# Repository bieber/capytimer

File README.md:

# CapyTimer

CapyTimer is meant to be a simple timer for
boxing/kickboxing/grappling/fitness.  My goal is to keep its interface
as simple as possible while maintaining the most important
functionality.  Work and rest times are set with dials, and the timing
started and stopped with a switch or button.  The display counts the
remaining time, the current round, and nothing else.

The display is constructed from WS2812B addressable LEDs.  The
original plan was to cut up and solder three-LED sections to create
the digits, but that proved time consuming and ugly so I ultimately
designed a PCB for the digits with the LEDs pre-placed.  You can
follow the original plan and save some money by cutting up and
soldering a WS2812B strip, or just order the PCBs preassembled from
JLC (or just get the boards manufactured and solder on the LEDs
yourself).

This isn't really meant to be a prescriptive set of instructions for
building the timer exactly a certain way.  I've provided components
here and I'll lay out a general path towards putting it together, but
you should feel free to substitute different controls and alter the
presentation to your liking.

**Warning** - The remote control design is currently untested.  I
*think* the parts will all fit properly, but I'm still waiting on the
final PCBs to test with and can't guarantee that the design works yet.

## Directory Structure

* `3d/` - Files for 3D printing.  These include the digit and
  separator diffusers, the remote control body, and a set of printed
  frames to hold the digits for testing purposes.
* `firmware/` - Code to run the AVR microcontroller.  Specifically
  this expects an Atmega328P, the avr-gcc toolchain and a USBasp
  programmer.  If you deviate from these specifications you may need
  to alter the firmware and makefile.
* `pcb/` - KiCad schematics and PCB designs.  This includes the main
  control board, boards with the LEDs laid out for the digits and
  separator, and a control board for the remote control.  With the
  exception of the remote control board (which is simple enough to
  easily hand solder), I've included gerbers and BOM/placement files
  that you can use to have the boards manufactured by JLCPCB.  These
  worked as of this publishing, but be warned that some parts may go
  out of stock and need replacing (they already switched to a new
  version of the WS2812B LEDs while I was working on the boards).
* `enclosure` - SVG designs to cut a front for the timer using the
  Shaper Origin.  You'll have to adapt these if you use a different
  CNC.

## Assembly Instructions

Please don't consider these instructions exhaustive, but more general
guidance.  You'll want to have some experience with electronics,
soldering and crimping connectors before getting started on this, as
well as some way to build an enclosure for the timer (I build mine out
of wood).

### Materials

| Part | Qty |
| ---- | --- |
| Control Board | 1 |
| Digit Board | 6 |
| Separator Board | 1 |
| Digit Diffuser | 6 |
| Separator Diffuser | 1 |
| M3x4.6x5.7mm Heat Set Inserts | 17 |
| M3x6 Screw | 14 |
| Linear Potentiometer (somewhere in the neighborhood of 10k) | 4 |
| Push Button | 2 |
| JST-PH Connector (3 pin) | 20 |
| JST-PH Connector (2 pin) | 4 |
| DC Barrel Connector | 1 |
| Right Angle Header (Female, 2.54mm) | 14 pins |
| Header (Male, 2.54mm) | 3 pins |
| Header Jumper | 1 |
| AVR-ISP 6 Pin Box Header | 1 |
| 3386P Potentiometer | 2 |
| 10k Through Hole Resistor | 2 |
| QIACHIP 433Mhz Transmitter/Receiver Set | 1 |
| Remote Control Parts | 1 set |
| M3x12 Screw | 3 |
| 5x1mm Round Magnet | 8 |
| AAA Battery Contact Plate | 4 |

Note that this doesn't include surface-mount components on the PCB,
only the parts you'll need to manually assemble.  If you intend to
hand solder the PCBs, consult the schematics for part listings.

### The Display

The display uses six digits and one separator between the minutes and
seconds.  You can have the digits and separator LEDs pre-assembled on
a PCB by JLCPCB using the files in the `pcb/` directory, or you can
buy a strip of WS2812B LEDs and glue them into the 3D printed
diffusers.  If you do so, you'll want to use 3 LEDs per digit segment
and one for each of the dots in the separator.  The LEDs should be
laid out in the same order that segments normally come in a seven
segment display.

If you get your LED PCBs pre-assembled, you'll still need to solder on
the connectors.  Use one three-pin JST-PH connector for each
connection.  Be sure to solder these on the back side of the board so
you can plug in to them while the front of the board is seated in the
diffuser.

When printing the plastic diffusers, I like to use white filament for
the first few layers and then switch to black.  This will minimize
light bleeding between segments while the display is in use.  If you
use PCBs for the digits and separator, the diffusers have holes for
threaded inserts.  You can then use the M3x6 screws to attach the
boards to the diffusers.

### The Control Board

Assuming you get the control board assembled by JLCPCB or some other
manufacturer, you'll just need to solder the connectors and a few
potentiometers onto the control board.  These include the DC barrel
jack for power, JST-PH connections for the screen, potentiometers and
push buttons, the AVR-ISP header, the header for the diagnostic jumper
(optional) and the angled header for the QIACHIP receiver module
(optional, only required if you want to use the remote control).  The
two 3386P potentiometers are used for volume and brightess control and
should be soldered directly onto the board.

The `JRESET1` connector is currently unused and can be safely ignored.

To program the microcontroller, just connect the ISP header to a
USBasp programmer.  You'll need the avr-gcc toolchain and avrdude
installed.  You can then run `make fuse` to program the fuses on the
chip, and `make program` to transfer the firmware.  After that the
timer should just work when everything is plugged in.

### Connections

* Solder a DC barrel jack connector onto `J1` for power.
* Connect four potentiometers to the 3-pin JST-PH connectors on the
  top-left corner of the board.  These will set the minutes and
  seconds for the work and rest periods.  The names on the silk screen
  are abbreviations for the function of the potentiometer, e.g. `JWM1`
  is the connection for the potentiometer that controls the minutes of
  the work period.  For these connectors, pin 1 is ground, pin 2 is
  signal, and pin 3 is +5v.
* The display connects to `JOUT1` and `JOUT2` via 3-pin JST-PH
  connectors.  Pin 1 is ground, pin 2 is signal, pin 3 is +5v.  As
  long as you connect the same pins on each end of your cables
  everything should work.  The WS2812B LEDs are daisy chained, so
  `JOUT1` should connect to the `JIN1` connector of the first digit,
  then its `JOUT1` connector should connect to the `JOUT1` of the next
  digit, and so on.  Connect the digits and separator for the time
  first, and then the two digits for the round display.  Finally, you
  can connect `JOUT1` on the last digit to `JOUT2` on the control
  board.  This final connection is for power only, to reduce the
  current that needs to flow through the first connection between
  control board and digits.
* The start and stop buttons should connect to the 2-pin JST-PH
  connectors labeled `JSTART1` and `JSTOP1`.  `JRESET1` is unused.
  These connectors have no polarity, they just need to be normally
  open and close when the buttons are pushed.
* Connect an active piezo buzzer to the 2-pin JST-PH connector labeled
  `JBUZZ1`.
* You may optionally solder a 3 pin male header to `JDIAG1`.  Place a
  jumper across the right two pins for normal operation: shifting the
  jumper to the left will put the timer in diagnostic mode, which
  displays the raw ADC value from the work minutes potentiometer for
  debugging purposes.
* If you intend to use a remote control, solder 7 pin female header,
  preferably right-angle, to `JRF1`.  You can then insert a QIACHIP
  receiver module directly into the header.

### Enclosure

The enclosure is largely left as an exercise for the reader.  You'll
want to select potentiometers and push buttons that fit your desired
aesthetic, and you may also wish to add features like an on/off switch
and external power inlet to the enclosure.

Because of the size of the timer, I haven't included a 3D printed
enclosure design.  Even with a 400x400 print bed, it would be
prohibitive to fit all six digits and the controls.  I have, however,
included two 3D printed frames that can hold the digit diffusers up
(with CA glue).  These aren't suitable for production use, but served
me well during development.

For production use, I build my enclosures as open-backed wooden boxes
with a front panel that has pockets routed in for the digit diffusers,
controls and the piezo buzzer.  I use a Shaper Origin to make the cuts
in the front panel, and you can find the SVG files for my design in
the `enclosure/` directory.  I've only tested these with the Shaper,
and expect that other CNCs will probably need some work to adapt them.

### Remote Control (Optional)

With a QIACHIP receiver and transmitter set, you can also build a
remote control for your timer.  The `pcb/` directory includes a small
PCB to tie the QIACIP transmitter to some tactile push button switches
and two AAA batteries.

For the remote control board, you'll need to solder on two pull-up
resistors, two tactile push-button switches (use switches tall enough
to poke up through the remote body), and a connector for the batteries
(or just solder the battery connectors directly to the board).  Add
right-angle header for the QIACHIP transmitter, and solder on an
antenna to `JANT1`.

The top remote component has holes for three heat-set inserts and four
5x1mm magnets, which should be glued into place.  You'll also want to
glue in the four battery contact plates, alternating positive and
negative plates between the two battery slots.  Solder the two plates
at the bottom of the remote together, and then solder wires on to the
connectors towards the top.

Glue opposite-polarity magnets into the remote lid to hold it on to
the body.  You can then attach the PCB and the remote body bottom to
the top by using the three M3x12 screws.  This connection is
inherently weak because the stems holding everything together are
stressed perpendicular to their layers, so be careful not to tighten
the screws more than necessary to hold everything together.

## Afterword

This should give you a rough idea of how to assemble one of these
timers, but the instructions aren't exceedingly detailed and leave a
lot of room to make the project your own.  If you attempt to build one
and run into problems, feel free to submit an issue.  And if you come
up with a design improvement, pull requests are welcome.

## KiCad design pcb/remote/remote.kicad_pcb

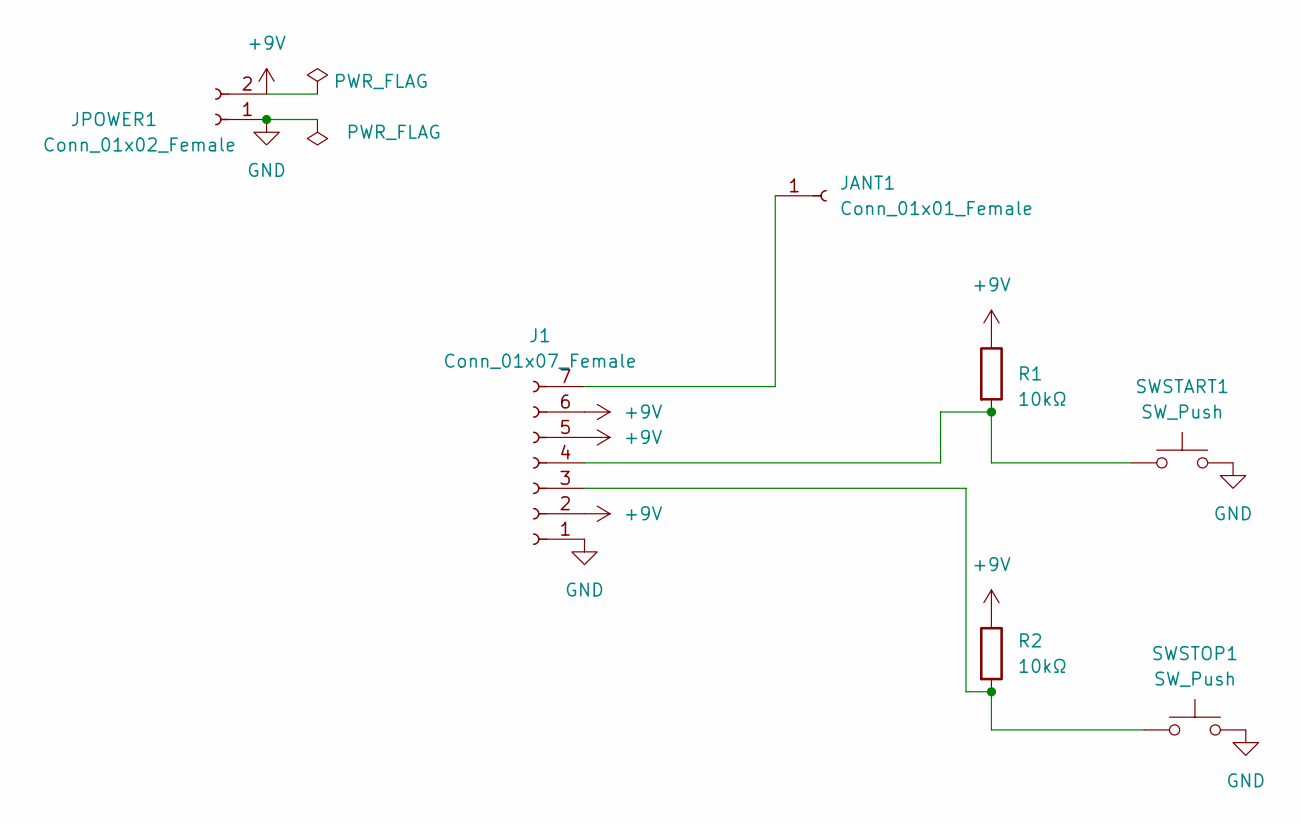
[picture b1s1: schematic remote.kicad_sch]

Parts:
J1: Conn_01x07_Female; PinHeader_1x07_P2.54mm_Vertical
JANT1: Conn_01x01_Female; PinHeader_1x01_P2.54mm_Vertical
JPOWER1: Conn_01x02_Female; JST_PH_B2B-PH-K_1x02_P2.00mm_Vertical
R1, R2: 10kΩ; R_Axial_DIN0207_L6.3mm_D2.5mm_P10.16mm_Horizontal; LCSC C25804
SWSTART1: SW_Push; SW_PUSH_6mm
SWSTOP1: SW_Push; SW_PUSH_6mm

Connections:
+9V: J1.2, J1.5, J1.6, JPOWER1.2, R1.1, R2.1
GND: J1.1, JPOWER1.1, SWSTART1.2, SWSTOP1.2
unnamed: J1.3, R2.2, SWSTOP1.1
unnamed: J1.4, R1.2, SWSTART1.1
unnamed: J1.7, JANT1.1

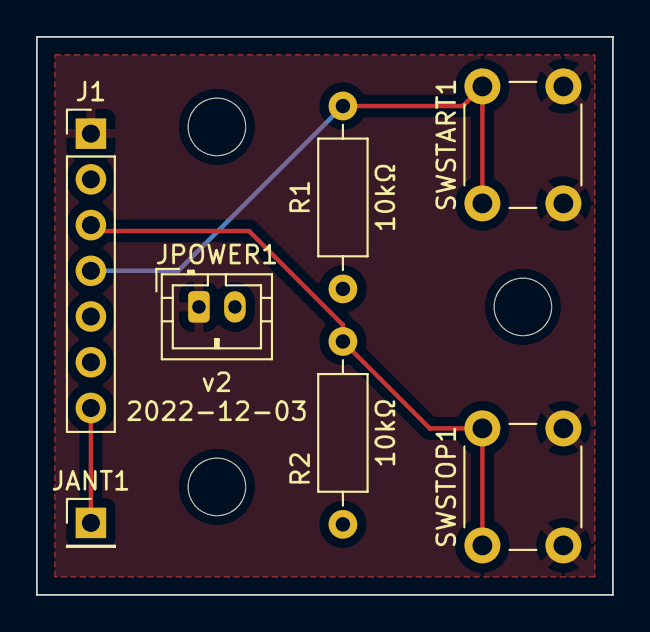
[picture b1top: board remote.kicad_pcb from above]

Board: 2 copper layers, 32.0 x 31.0 mm, 7 parts (0 on the bottom side), 5 nets.

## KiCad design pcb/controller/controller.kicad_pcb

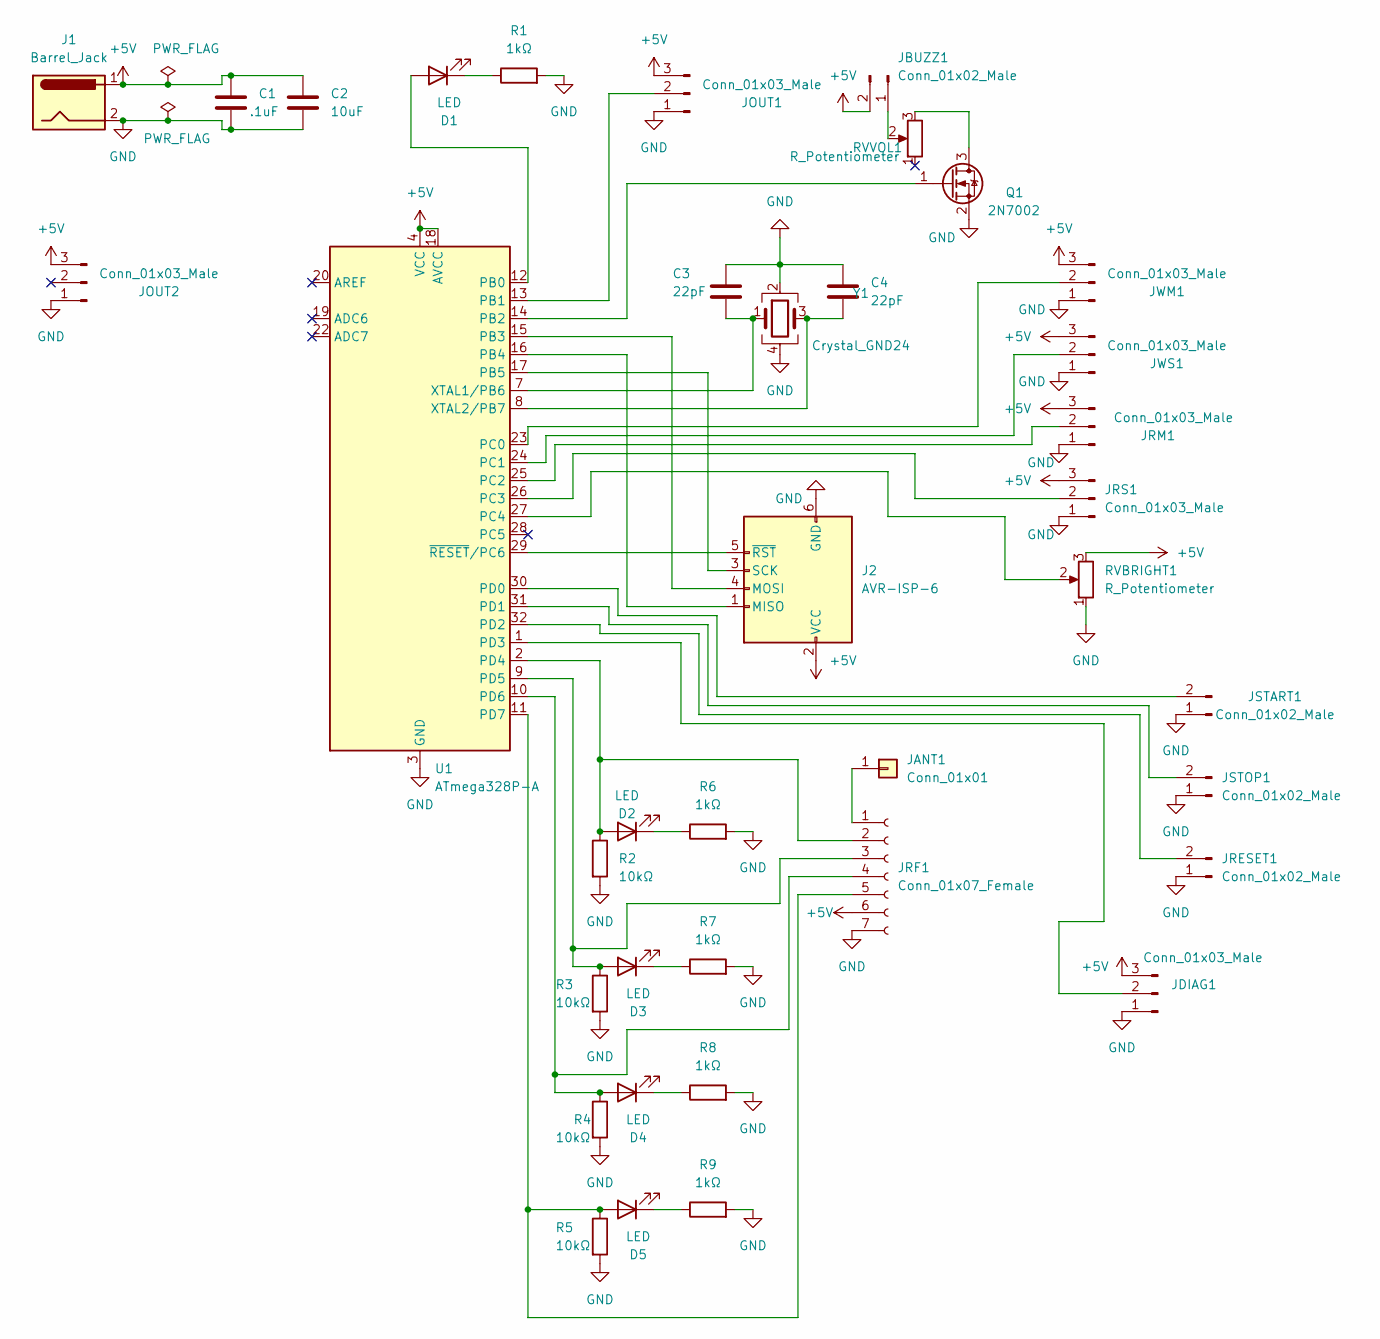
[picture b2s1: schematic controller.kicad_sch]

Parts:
C1: .1uF; C_0603_1608Metric; LCSC C14663
C2: 10uF; C_0805_2012Metric; LCSC C15850
C3, C4: 22pF; C_0402_1005Metric; LCSC C1555
D1, D2, D3, D4, D5: LED; LED_0805_2012Metric; LCSC C2297
J1: Barrel_Jack; BarrelJack_Horizontal
J2: AVR-ISP-6; IDC-Header_2x03_P2.54mm_Vertical
JANT1: Conn_01x01; PinHeader_1x01_P2.54mm_Vertical
JBUZZ1: Conn_01x02_Male; JST_PH_B2B-PH-K_1x02_P2.00mm_Vertical
JDIAG1: Conn_01x03_Male; PinHeader_1x03_P2.54mm_Vertical
JOUT1, JOUT2: Conn_01x03_Male; JST_PH_B3B-PH-K_1x03_P2.00mm_Vertical
JRESET1: Conn_01x02_Male; JST_PH_B2B-PH-K_1x02_P2.00mm_Vertical
JRF1: Conn_01x07_Female; PinHeader_1x07_P2.54mm_Vertical
JRM1: Conn_01x03_Male; JST_PH_B3B-PH-K_1x03_P2.00mm_Vertical
JRS1: Conn_01x03_Male; JST_PH_B3B-PH-K_1x03_P2.00mm_Vertical
JSTART1: Conn_01x02_Male; JST_PH_B2B-PH-K_1x02_P2.00mm_Vertical
JSTOP1: Conn_01x02_Male; JST_PH_B2B-PH-K_1x02_P2.00mm_Vertical
JWM1: Conn_01x03_Male; JST_PH_B3B-PH-K_1x03_P2.00mm_Vertical
JWS1: Conn_01x03_Male; JST_PH_B3B-PH-K_1x03_P2.00mm_Vertical
Q1: 2N7002; SOT-23; LCSC C8545
R1, R6, R7, R8, R9: 1kΩ; R_0603_1608Metric; LCSC C21190
R2, R3, R4, R5: 10kΩ; R_0603_1608Metric; LCSC C25804
RVBRIGHT1: R_Potentiometer; Potentiometer_Bourns_3386P_Vertical
RVVOL1: R_Potentiometer; Potentiometer_Bourns_3386P_Vertical
U1: ATmega328P-A; TQFP-32_7x7mm_P0.8mm; LCSC C14877
Y1: Crystal_GND24; Crystal_SMD_3225-4Pin_3.2x2.5mm; LCSC C431155

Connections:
+5V: C1.1, C2.1, J1.1, J2.2 (VCC), JBUZZ1.2, JDIAG1.3, JOUT1.3, JOUT2.3, JRF1.6, JRM1.3, JRS1.3, JWM1.3, JWS1.3, RVBRIGHT1.3, U1.4 (VCC), U1.6 (VCC), U1.18 (AVCC)
GND: C1.2, C2.2, C3.1, C4.1, J1.2, J2.6 (GND), JDIAG1.1, JOUT1.1, JOUT2.1, JRESET1.1, JRF1.7, JRM1.1, JRS1.1, JSTART1.1, JSTOP1.1, JWM1.1, JWS1.1, Q1.2 (S), R1.2, R2.2, R3.2, R4.2, R5.2, R6.2, R7.2, R8.2, R9.2, RVBRIGHT1.1, U1.3 (GND), U1.5 (GND), U1.21 (GND), Y1.2, Y1.4
unnamed: C3.2, U1.7 (XTAL1/PB6), Y1.1
unnamed: C4.2, U1.8 (XTAL2/PB7), Y1.3
unnamed: D1.1 (K), R1.1
unnamed: D1.2 (A), U1.12 (PB0)
unnamed: D2.1 (K), R6.1
unnamed: D2.2 (A), JRF1.2, R2.1, U1.2 (PD4)
unnamed: D3.1 (K), R7.1
unnamed: D3.2 (A), JRF1.3, R3.1, U1.9 (PD5)
unnamed: D4.1 (K), R8.1
unnamed: D4.2 (A), JRF1.4, R4.1, U1.10 (PD6)
unnamed: D5.1 (K), R9.1
unnamed: D5.2 (A), JRF1.5, R5.1, U1.11 (PD7)
unnamed: J2.1 (MISO), U1.16 (PB4)
unnamed: J2.3 (SCK), U1.17 (PB5)
unnamed: J2.4 (MOSI), U1.15 (PB3)
unnamed: J2.5 (~RST), U1.29 (~RESET/PC6)
unnamed: JANT1.1, JRF1.1
unnamed: JBUZZ1.1, RVVOL1.2
unnamed: JDIAG1.2, U1.1 (PD3)
unnamed: JOUT1.2, U1.13 (PB1)
unnamed: JRESET1.2, U1.32 (PD2)
unnamed: JRM1.2, U1.25 (PC2)
unnamed: JRS1.2, U1.26 (PC3)
unnamed: JSTART1.2, U1.30 (PD0)
unnamed: JSTOP1.2, U1.31 (PD1)
unnamed: JWM1.2, U1.23 (PC0)
unnamed: JWS1.2, U1.24 (PC1)
unnamed: Q1.1 (G), U1.14 (PB2)
unnamed: Q1.3 (D), RVVOL1.3
unnamed: RVBRIGHT1.2, U1.27 (PC4)

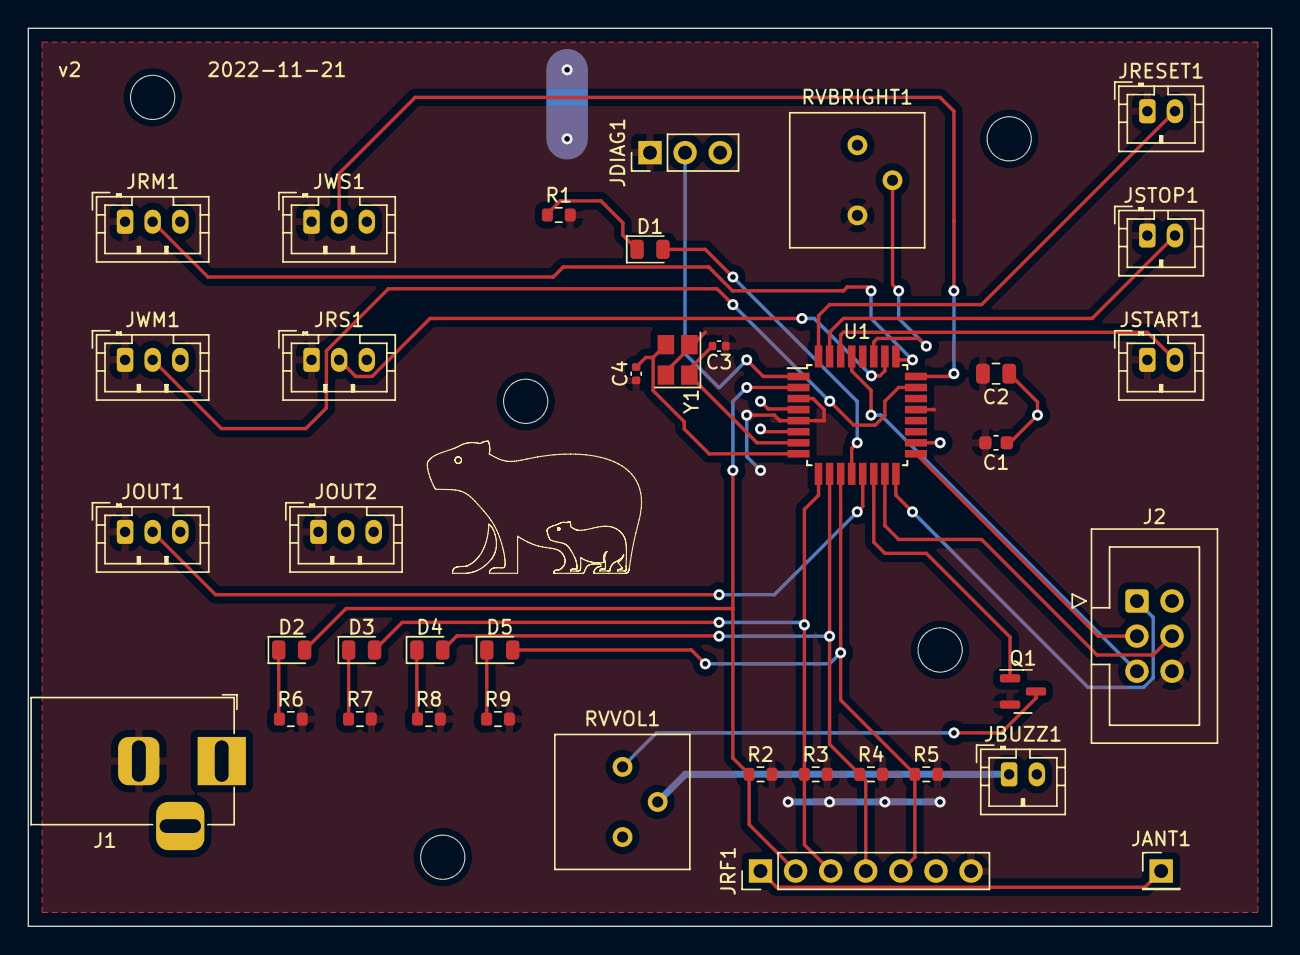
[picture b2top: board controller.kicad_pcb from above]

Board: 2 copper layers, 90.0 x 65.0 mm, 38 parts (0 on the bottom side), 32 nets.

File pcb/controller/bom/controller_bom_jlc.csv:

"Comment","Designator","Footprint","LCSC"
".1uF","C1","C_0603_1608Metric","C14663"
"10uF","C2","C_0805_2012Metric","C15850"
"22pF","C3,C4","C_0402_1005Metric","C1555"
"LED","D1,D2,D3,D4,D5","LED_0805_2012Metric","C2297"
"2N7002","Q1","SOT-23","C8545"
"1kΩ","R1,R6,R7,R8,R9","R_0603_1608Metric","C21190"
"10kΩ","R2,R3,R4,R5","R_0603_1608Metric","C25804"
"ATmega328P-A","U1","TQFP-32_7x7mm_P0.8mm","C14877"
"Crystal_GND24","Y1","Crystal_SMD_3225-4Pin_3.2x2.5mm","C431155"

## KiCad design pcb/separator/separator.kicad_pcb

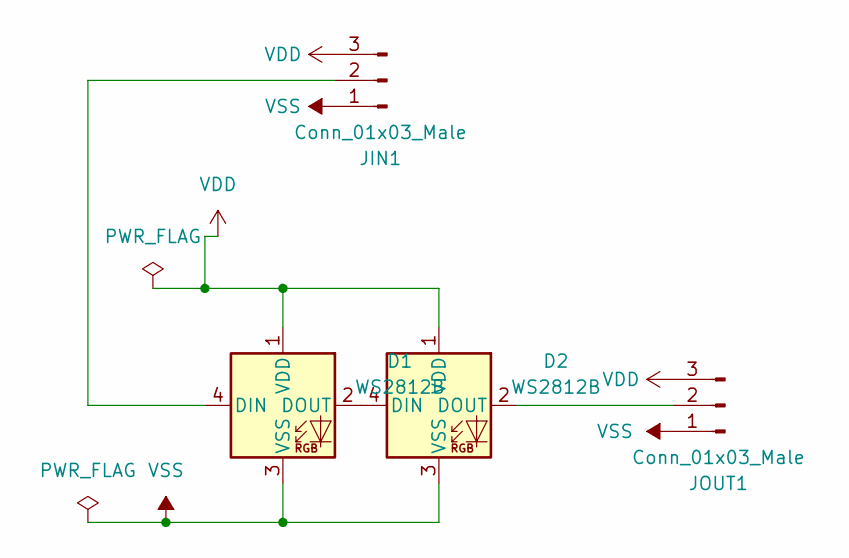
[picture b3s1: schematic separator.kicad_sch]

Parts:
D1, D2: WS2812B; LED_WS2812B_PLCC4_5.0x5.0mm_P3.2mm; LCSC C2874885
JIN1: Conn_01x03_Male; JST_PH_B3B-PH-K_1x03_P2.00mm_Vertical
JOUT1: Conn_01x03_Male; JST_PH_B3B-PH-K_1x03_P2.00mm_Vertical

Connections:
unnamed: D1.2 (DOUT), D2.4 (DIN)
unnamed: D1.4 (DIN), JIN1.2
unnamed: D2.2 (DOUT), JOUT1.2
VDD: D1.1 (VDD), D2.1 (VDD), JIN1.3, JOUT1.3
VSS: D1.3 (VSS), D2.3 (VSS), JIN1.1, JOUT1.1

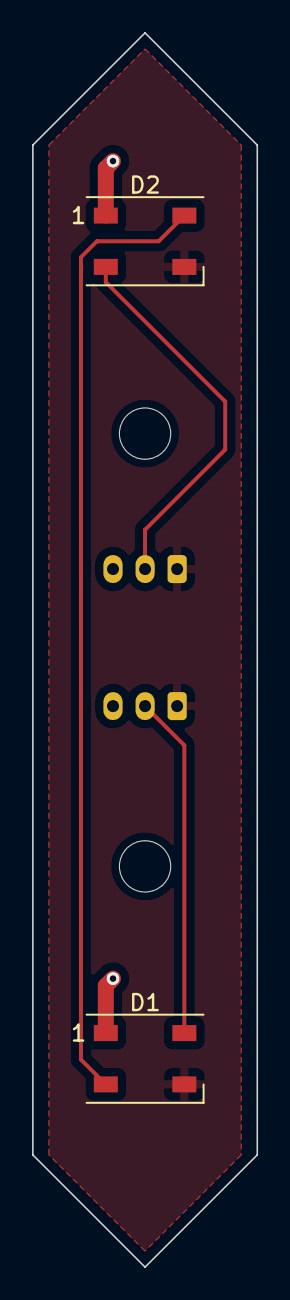
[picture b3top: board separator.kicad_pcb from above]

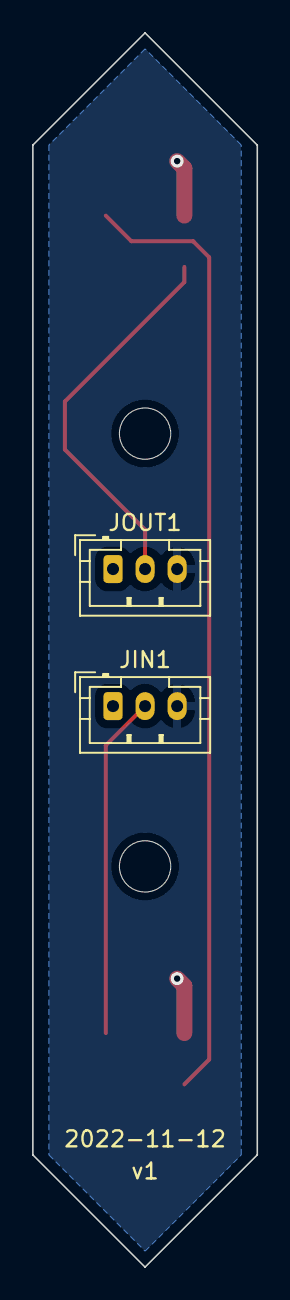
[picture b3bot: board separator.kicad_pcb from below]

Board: 2 copper layers, 14.0 x 77.0 mm, 4 parts (2 on the bottom side), 5 nets.

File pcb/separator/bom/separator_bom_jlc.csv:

"Comment","Designator","Footprint","LCSC"
"WS2812B","D1,D2","LED_WS2812B_PLCC4_5.0x5.0mm_P3.2mm","C2874885"

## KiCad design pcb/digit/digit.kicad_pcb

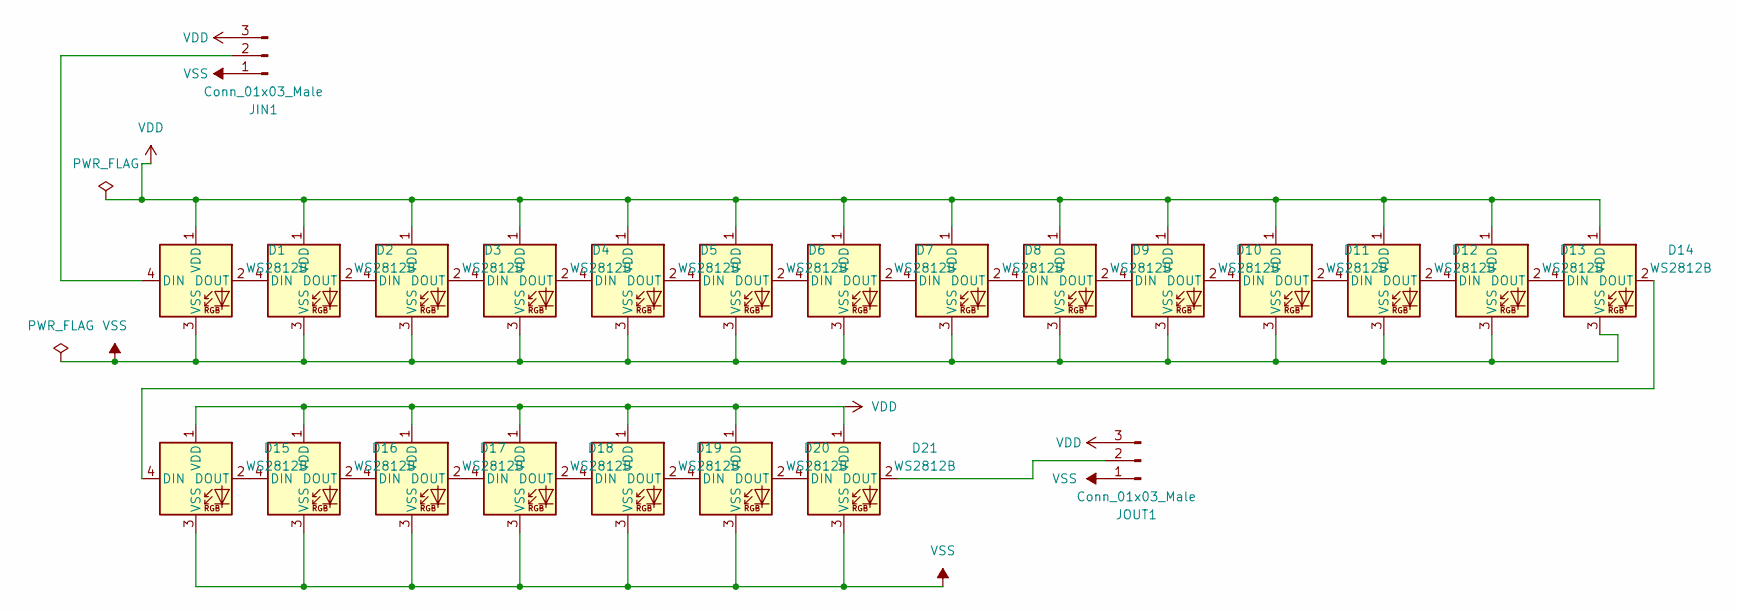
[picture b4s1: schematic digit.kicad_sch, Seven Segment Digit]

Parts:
D1, D2, D3, D4, D5, D6, D7, D8, D9, D10, D11, D12, D13, D14, D15, D16, D17, D18, D19, D20, D21: WS2812B; LED_WS2812B_PLCC4_5.0x5.0mm_P3.2mm; LCSC C2874885
JIN1: Conn_01x03_Male; JST_PH_B3B-PH-K_1x03_P2.00mm_Vertical
JOUT1: Conn_01x03_Male; JST_PH_B3B-PH-K_1x03_P2.00mm_Vertical

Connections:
unnamed: D1.2 (DOUT), D2.4 (DIN)
unnamed: D1.4 (DIN), JIN1.2
unnamed: D2.2 (DOUT), D3.4 (DIN)
unnamed: D3.2 (DOUT), D4.4 (DIN)
unnamed: D4.2 (DOUT), D5.4 (DIN)
unnamed: D5.2 (DOUT), D6.4 (DIN)
unnamed: D6.2 (DOUT), D7.4 (DIN)
unnamed: D7.2 (DOUT), D8.4 (DIN)
unnamed: D8.2 (DOUT), D9.4 (DIN)
unnamed: D10.2 (DOUT), D11.4 (DIN)
unnamed: D9.2 (DOUT), D10.4 (DIN)
unnamed: D11.2 (DOUT), D12.4 (DIN)
unnamed: D12.2 (DOUT), D13.4 (DIN)
unnamed: D13.2 (DOUT), D14.4 (DIN)
unnamed: D14.2 (DOUT), D15.4 (DIN)
unnamed: D15.2 (DOUT), D16.4 (DIN)
unnamed: D16.2 (DOUT), D17.4 (DIN)
unnamed: D17.2 (DOUT), D18.4 (DIN)
unnamed: D18.2 (DOUT), D19.4 (DIN)
unnamed: D19.2 (DOUT), D20.4 (DIN)
unnamed: D20.2 (DOUT), D21.4 (DIN)
unnamed: D21.2 (DOUT), JOUT1.2
VDD: D1.1 (VDD), D2.1 (VDD), D3.1 (VDD), D4.1 (VDD), D5.1 (VDD), D6.1 (VDD), D7.1 (VDD), D8.1 (VDD), D9.1 (VDD), D10.1 (VDD), D11.1 (VDD), D12.1 (VDD), D13.1 (VDD), D14.1 (VDD), D15.1 (VDD), D16.1 (VDD), D17.1 (VDD), D18.1 (VDD), D19.1 (VDD), D20.1 (VDD), D21.1 (VDD), JIN1.3, JOUT1.3
VSS: D1.3 (VSS), D2.3 (VSS), D3.3 (VSS), D4.3 (VSS), D5.3 (VSS), D6.3 (VSS), D7.3 (VSS), D8.3 (VSS), D9.3 (VSS), D10.3 (VSS), D11.3 (VSS), D12.3 (VSS), D13.3 (VSS), D14.3 (VSS), D15.3 (VSS), D16.3 (VSS), D17.3 (VSS), D18.3 (VSS), D19.3 (VSS), D20.3 (VSS), D21.3 (VSS), JIN1.1, JOUT1.1

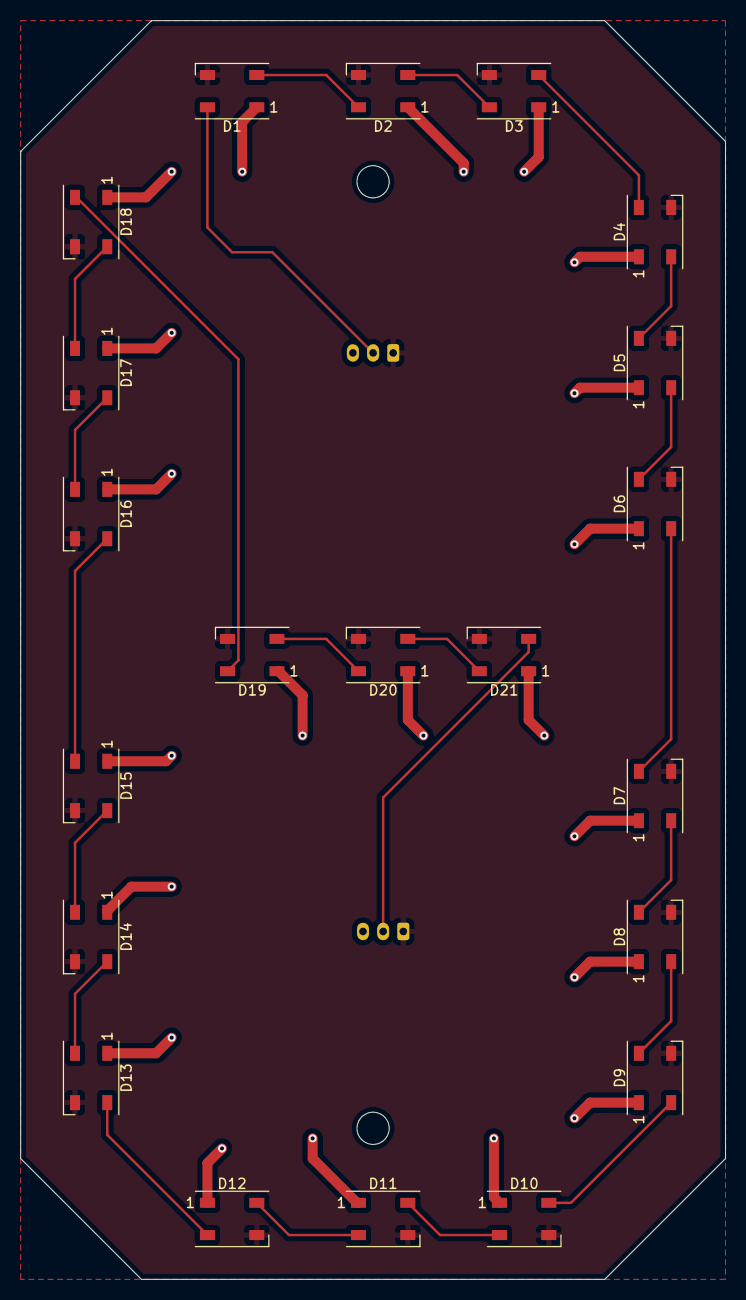
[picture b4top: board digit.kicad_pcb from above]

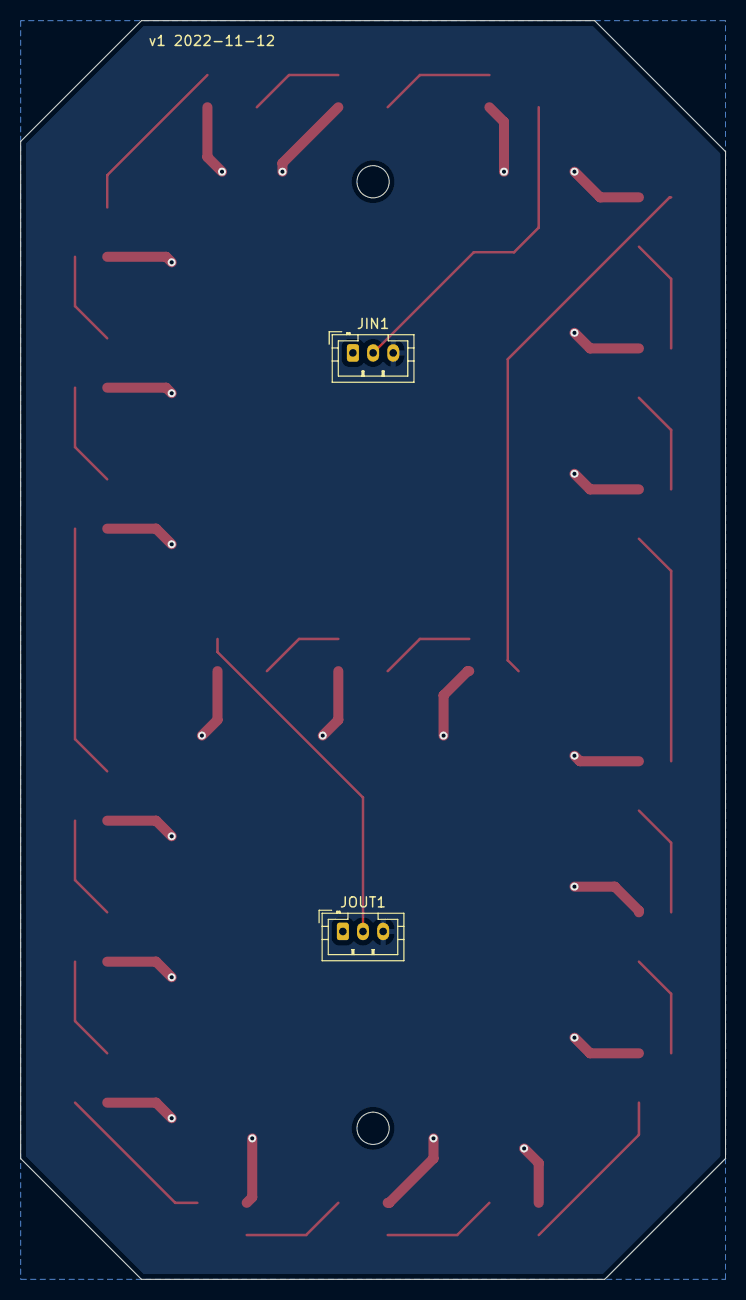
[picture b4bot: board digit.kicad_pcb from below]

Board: 2 copper layers, 70.0 x 125.0 mm, 23 parts (2 on the bottom side), 24 nets.

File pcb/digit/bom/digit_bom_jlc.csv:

"Comment","Designator","Footprint","LCSC"
"WS2812B","D1,D2,D3,D4,D5,D6,D7,D8,D9,D10,D11,D12,D13,D14,D15,D16,D17,D18,D19,D20,D21","LED_WS2812B_PLCC4_5.0x5.0mm_P3.2mm","C2874885"

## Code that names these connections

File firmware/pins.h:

/*
 * Copyright (C) 2022, Robert Bieber
 *
 * This program is free software: you can redistribute it and/or
 * modify it under the terms of the GNU General Public License as
 * published by the Free Software Foundation, either version 3 of the
 * License, or (at your option) any later version.
 *
 * This program is distributed in the hope that it will be useful, but
 * WITHOUT ANY WARRANTY; without even the implied warranty of
 * MERCHANTABILITY or FITNESS FOR A PARTICULAR PURPOSE.  See the GNU
 * General Public License for more details.
 *
 * You should have received a copy of the GNU General Public License
 * along with this program.  If not, see
 * <https://www.gnu.org/licenses/>.
 */

#ifndef PINS_H
#define PINS_H

#include <avr/io.h>

#define SCREEN_SIZE 384

#define DDR_STATUS DDRB
#define PORT_STATUS PORTB
#define PIN_STATUS PB0

#define DDR_SCREEN DDRB
#define PORT_SCREEN PORTB
#define PIN_SCREEN PB1

#define DDR_BUZZ DDRB
#define PORT_BUZZ PORTB
#define PIN_BUZZ PB2

#define DDR_START DDRD
#define PULLUP_START PORTD
#define PORT_START PIND
#define PIN_START PD0

#define DDR_STOP DDRD
#define PULLUP_STOP PORTD
#define PORT_STOP PIND
#define PIN_STOP PD1

#define DDR_RF_START DDRD
#define PULLUP_RF_START PORTD
#define PORT_RF_START PIND
#define PIN_RF_START PD4

#define DDR_RF_STOP DDRD
#define PULLUP_RF_STOP PORTD
#define PORT_RF_STOP PIND
#define PIN_RF_STOP PD5

#define DDR_DIAGNOSTIC DDRD
#define PULLUP_DIAGNOSTIC PORTD
#define PORT_DIAGNOSTIC PIND
#define PIN_DIAGNOSTIC PD3

#define ADC_WORK_MINUTES 0
#define ADC_WORK_SECONDS 1
#define ADC_REST_MINUTES 2
#define ADC_REST_SECONDS 3
#define ADC_BRIGHTNESS 4

// Turn timer 0 on with a 1024 prescaler
#define TIMER_0_ON ((1 << CS02) | (1 << CS00))
#define TIMER_0_OFF (~((1 << CS02) | (1 << CS01) | (1 << CS00)))

// Turn timer 1 on with a 1024 prescaler
#define TIMER_1_ON ((1 << CS12) | (1 << CS10))
#define TIMER_1_OFF (~((1 << CS12) | (1 << CS11) | (1 << CS10)))

// Turn timer 2 on with a 1024 prescaler
#define TIMER_2_ON ((1 << CS22) | (1 << CS21) | (1 << CS00))
#define TIMER_2_OFF (~((1 << CS22) | (1 << CS21) | (1 << CS20)))

#endif

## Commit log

2022-10-16 Initial Commit
    This is the very beginning of the project. The firmware doesn't
    really do anything useful yet, but I have implemented WS2812B control
    in assembly for an ATTiny running at 20MHz and designed a digit and a
    colon separator to fit the LEDs into.
2022-10-21 PCB Mount Points in 3D Models
    I'm going to use PCBs with LEDs mounted instead of manually soldering
    LED strips together, so this adds some mount points to the digit and
    diffuser 3D models to fit M3 heated inserts.
2022-10-21 Added LEDs To Test Code
    Still nothing really notable going on in the firmware, but I bumped up
    the size of the pixel value buffer for testing with a full digit. I
    also realized that having the firmware gitignore'd also ignored the
    directory, so I just checked it in.
2022-10-21 Digit PCB Design
    This is my first iteration of the PCB design for the digits, which
    will be chained together with JST connectors. It's also my first PCB
    design ever, so absolutely no guarantees that it's any good.
2022-10-22 Playing With Digits
    This adds some basic digit-handling code that just cycles one digit
    with varying colors. Unfortunately using a generous
    three-bytes-per-pixel isn't going to work if I want to stick with the
    ATTiny, so the next step will be to write up a more efficient encoding
    of the pixel data.
2022-10-23 Playing With ADC and Digits
    I'm beginning to experiment with the ADC and a couple of WS2812B
    digits. I only have two for now, so I'm just testing using
    potentiometers to set the minute components of the work and rest
    times.
    It wasn't feasible to cram a decoder for a more memory-efficient type
    of storage into the digit writing routine, so I just went ahead and
2022-10-25 Counting Down
    This gets me to a point where the timer actually, well, times, albeit
    with only two digits. I've got the 16 bit counter in action to count
    off the seconds and rearranged the main loop to work as a state
    machine with some global state to make it all work with the timer
    interrupt.
2022-10-26 Starting Control Board Schematic
    This gets the control board schematic started, but not complete yet.
2022-10-31 Buzzer Tests
    Doing some initial testing with a piezo buzzer, I'll make this more
    sophisticated with one of the timers next.
2022-10-31 More Controller Updates
    Continuing to work on the controller board schematic
2022-11-01 First Draft of Control Board
    This completes the first draft of the control board schematic, adding
    the RF module inputs and the connectors for the start/stop/reset
    buttons.
2022-11-01 Control Board PCB Layout
    This is a first stab at the PCB layout for the control board.
2022-11-05 Controller PCB Diagnostic Header
    This adds a diagnostic header that I'll be able to put a jumper on to
    turn on diagnostic mode--which will be used to calibrate the
    potentiometer inputs. In addition to adding this to the PCB layout, I
    rearranged a few components and cleaned up some traces.
2022-11-05 Added Capy Logo to Controller Board
2022-11-05 Silkscreen Cleanup
    Removed the placeholder Ref** text from the mounting holes in the
    digit and control PCBs
2022-11-06 Test Frames and Diffuser Updates
    I reduced the height of the diffusers to 15mm for better brightness,
    and added models for some frames to hold the digits for testing.
2022-11-06 Added Volume Control
    This adds a volume control potentiometer to the schematic and PCB
    design for the control board
2022-11-06 Firmware Cleanup
    I've got all the test hardware set up now, so at this point it's time
    to stop toying around with demo code and start writing a serious
    firmware. To that end, I made a handful of enhancements here that
    shouldn't materially affect the behavior:
    * Added missing copyright headers
    * Defined constants for all of the I/O pins
2022-11-06 Fleshed Out LED Display
    This adds a full display of the working time with divider instead of
    just using the first two digits for the seconds. I also added a round
    display in blue.
2022-11-06 Reading Minutes
    This moves the time-reading code into a single `debounce_time`
    function that reads both minutes and seconds, and includes both of
    them in the result. I'm using that function to read the work and rest
    times now so work and rest times are now fully settable.
2022-11-07 Timing Cycle Refactor
    This moves state transitions in the timing lifecycle out into their
    own functions to clean up the main loop a little.
2022-11-07 Temporary Rest Time Display
    Previously, when the timer wasn't active we would just show whatever
    time was most recently altered. This changes it so that we always
    show the work time by default, since that's the time that will take
    effect right away when the user pushes the start button. The rest
    time will show while the user is adjusting it, and then for five
    seconds afterwards.
2022-11-07 Buzzer Implementation
    This replaces the old, somewhat janky buzzer implementation with
    something closer to how I want the final product to behave with an
    alternating buzz for starting the work time and a solid one for
    starting the rest time. I also handled the edge cases when the timer
    runs with either the rest or the work time set to zero, in which case
    we just repeat the one time that is set over and over again.
2022-11-08 Added MOSFET to Controller Board for Buzzer
    I want to allow the use of some higher powered piezo buzzers, so this
    adds a MOSFET to switch the buzzer current instead of connecting it
    directly to the Atmega pin.
2022-11-09 Added Separator PCB And Build Files
    This adds a simple PCB with 2 WS2812B LEDs for the center separator.
    I also generated gerber, BOM and pick and place files for all the
    boards and updated the part numbers for the WS2812B LEDs to the new
    version that JLCPCB carries.
2022-11-10 Adjustable Brightness
    This adds an ADC input (hooked up to a potentiometer) to set the
    display brightness in five separate levels. For the debounce function
    I manually set a series of thresholds, which is a model I'll be moving
    all of the ADC debounce functions to in the next couple of commits as
    it enables profiling a potentiometer with a non-linear response. I
    also noticed that I'd accidentally left some `else if (0)` blocks in
2022-11-12 Added Diagnostic Mode
    This adds a diagnostic mode to the firmware. By connecting a pin to
    ground (which will be a header + jumper on the final control board)
    you can put it into a mode where it just draws the raw value of the
    work minute pot to the screen. This will make it possible to profile
    potentiometers to compensate for any non-linearity
2022-11-13 PCB Touchup
    Two changes in this commit.
    1. I rewired the volume potentiometer so that the MOSFET is now the
    closest thing to ground. That way we'll always be sure to have
    sufficient gate-source voltage to trigger it when the buzzer is turned
    on.
    2. I added v1/date indicators to the silk screen layers of all the
2022-11-20 Debounce Refactor and RF Button Addition
    This adds pins for and checks an RF receiver for use as a remote
    control. Along the way I refactored the button debouncing so that
    buttons will now fire once and not fire again until they've fully
    reset. This is used for all buttons now and obviates the check for
    button release after pause.
2022-11-21 Adapt Firmware to Atmega328P
    This updates the Makefile and pin assignments to fit the actual
    configuration of the control board. Now that I've received a batch of
    the boards, I'll be using one for development from here on out.
2022-11-21 Bump Up LED Resistors
    The LEDs on the controller board are very bright in the first batch of
    boards, so this replaces the 470ohm resistors with 1k resistors to dim
    them a little.
2022-11-23 Remove Debug Code
    I accidentally left in some code I'd been using to debug a while back,
    this restores diagnostic mode to its normal functionality.
2022-11-27 Enclosure First Steps
    This adds my first attempt at an enclosure design as SVG files for
    cutting with the Shaper Origin. These haven't been tested yet and
    will probably need some tweaks.
2022-11-27 Added Remote PCB
    This adds a simple little PCB design to mount a QIACHIP 433Mhz
    transmitter and connect it to a couple of buttons and an antenna. I
    used through-hole resistors in this board because it just didn't make
    sense to pay for SMT assembly when the two resistors are the only
    components on the board.
2022-11-28 Enclosure SVG Updates
    Two fixes here. First, I updated the digit segment cutouts to use
    inside line cuts. I also added a custom anchor point to the front
    template, so you can grid off of the digit cutouts at the top left and
    not have to do any math to get the text aligned properly.
2022-12-03 Remote PCB Update
    This updates the remote control PCB to use tactile switches directly
    on the board instead of buttons connected via JST connector.
2022-12-04 Started Working on Remote Design
    I'm just getting started putting together a remote that will connect a
    QIACHIP transmitter to a couple of buttons and a 9v battery. This
    adds just the top half of the shell.
2022-12-05 Continuing Remote Work
    This adds a bottom portion and battery holder to the remote control
    design with the battery lid beginning to take shape.
2022-12-06 Added Remote Battery Lid
    This adds the battery lid with magnets for the remote control. At
    this point the design should be functional, however it feels very
    awkward in the hand and I think I'm going to redesign it for a pair of
    AAA batteries instead.
2022-12-06 Remote AAA Redesign: Top
    This is the first part of a remote control redesign to use two AAA
    batteries instead of one 9v. This includes an updated top component
    with a battery compartment built in.
2022-12-07 AAA Remote v1
    This is the first full design of the AAA-based remote control. I've
    tested the fit with the threaded inserts and screws and magnets, but
    I'm still waiting on the battery contacts and PCBs to arrive and may
    need to change the design slightly to accommodate them.
2022-12-10 Fix Discontinuities in Enclosure Cut File
    The FreeCAD export I used to lay out the cut paths for the seven
    segment digits had a bunch of open paths for the actual segments. For
    some reason the Origin *mostly* took these paths in stride, but a few
    of them would show up as on line cuts instead of inside cuts on the
    device and need manual correction. This fixes the paths so they
    should cut correctly by default.
2022-12-11 Rotated Remote Top
    This includes a new STL file for the top component of the remote that
    doesn't require manual rotation when slicing. At this point the
    components all appear to fit in the remote, so I think this is going
    to be the final design. Ideally I'd like to tweak the battery
    compartment a little more, but I've made such a mess referencing
    external geometry that it's just too difficult to make those kinds of
2022-12-15 README Update
    This updates the README with a rough set of instructions for building
    the timer.
2022-12-22 Remove Remote Screws
    Since it's so easy to break off the stems by overtightening the remote
    screws, I'm removing the holes for them from the back. The board will
    still screw down to the top piece, but sealing up the shell will be
    done with super glue now. This isn't ideal for repairability, but
    should hold up better in practice.
2022-12-23 Restored Missing Fillet
2022-12-29 STL Fixup
    I mixed up the STL files when exporting after the last change, this
    should get the remote files all sorted out.
